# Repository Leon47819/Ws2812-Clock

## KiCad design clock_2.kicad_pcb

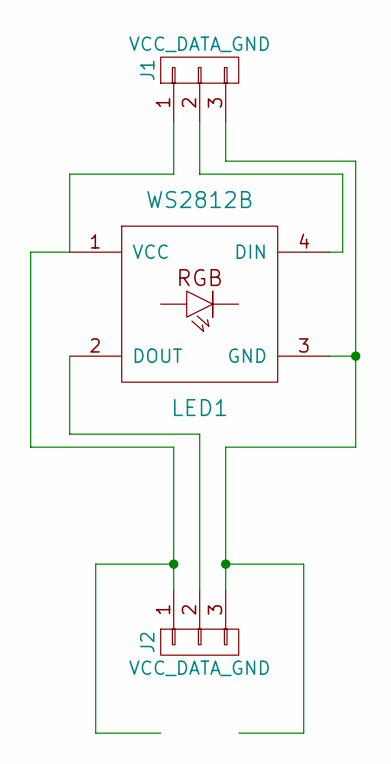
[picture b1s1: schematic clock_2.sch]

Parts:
J1, J2: VCC_DATA_GND; Pin_Header_Straight_1x03_Pitch2.54mm
LED1: WS2812B

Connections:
unnamed: J1.1, J2.1, LED1.1 (VCC)
unnamed: J1.2, LED1.4 (DIN)
unnamed: J1.3, J2.3, LED1.3 (GND)
unnamed: J2.2, LED1.2 (DOUT)

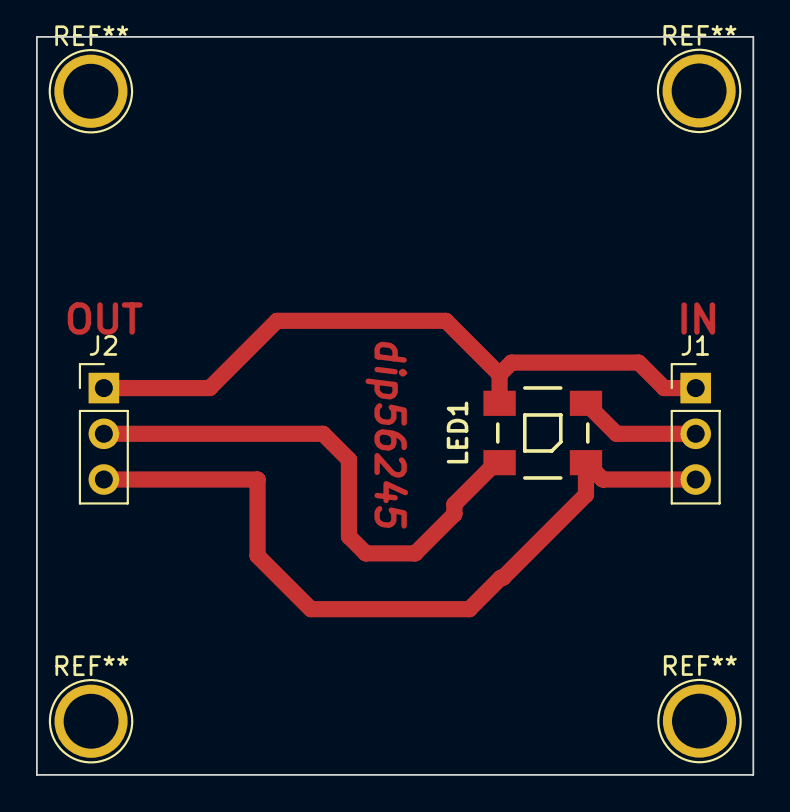
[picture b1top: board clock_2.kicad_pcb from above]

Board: 2 copper layers, 39.8 x 41.0 mm, 3 parts (0 on the bottom side), 4 nets.

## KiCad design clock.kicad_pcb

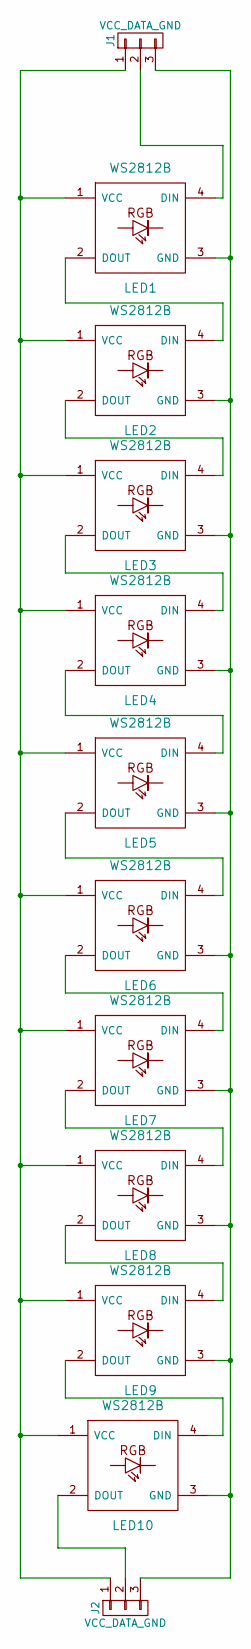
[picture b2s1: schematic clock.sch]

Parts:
J1, J2: VCC_DATA_GND; Pin_Header_Straight_1x03_Pitch2.54mm
LED1, LED2, LED3, LED4, LED5, LED6, LED7, LED8, LED9, LED10: WS2812B

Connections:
unnamed: J1.1, J2.1, LED1.1 (VCC), LED2.1 (VCC), LED3.1 (VCC), LED4.1 (VCC), LED5.1 (VCC), LED6.1 (VCC), LED7.1 (VCC), LED8.1 (VCC), LED9.1 (VCC), LED10.1 (VCC)
unnamed: J1.2, LED1.4 (DIN)
unnamed: J1.3, J2.3, LED1.3 (GND), LED2.3 (GND), LED3.3 (GND), LED4.3 (GND), LED5.3 (GND), LED6.3 (GND), LED7.3 (GND), LED8.3 (GND), LED9.3 (GND), LED10.3 (GND)
unnamed: J2.2, LED10.2 (DOUT)
unnamed: LED1.2 (DOUT), LED2.4 (DIN)
unnamed: LED2.2 (DOUT), LED3.4 (DIN)
unnamed: LED3.2 (DOUT), LED4.4 (DIN)
unnamed: LED4.2 (DOUT), LED5.4 (DIN)
unnamed: LED5.2 (DOUT), LED6.4 (DIN)
unnamed: LED6.2 (DOUT), LED7.4 (DIN)
unnamed: LED7.2 (DOUT), LED8.4 (DIN)
unnamed: LED8.2 (DOUT), LED9.4 (DIN)
unnamed: LED9.2 (DOUT), LED10.4 (DIN)

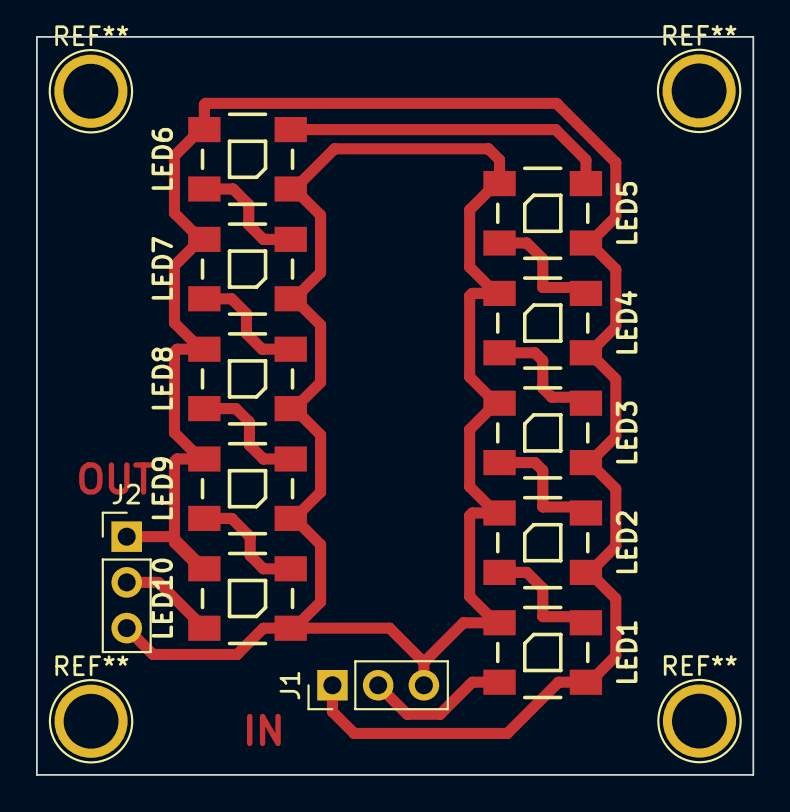
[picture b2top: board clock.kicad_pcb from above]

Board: 2 copper layers, 39.8 x 41.0 mm, 12 parts (0 on the bottom side), 13 nets.

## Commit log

2017-08-10 init
